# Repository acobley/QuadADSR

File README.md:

View this project on [CADLAB.io](https://cadlab.io/project/1256/master/files). 

# QuadADSR
A Quad Eurorack ADSR

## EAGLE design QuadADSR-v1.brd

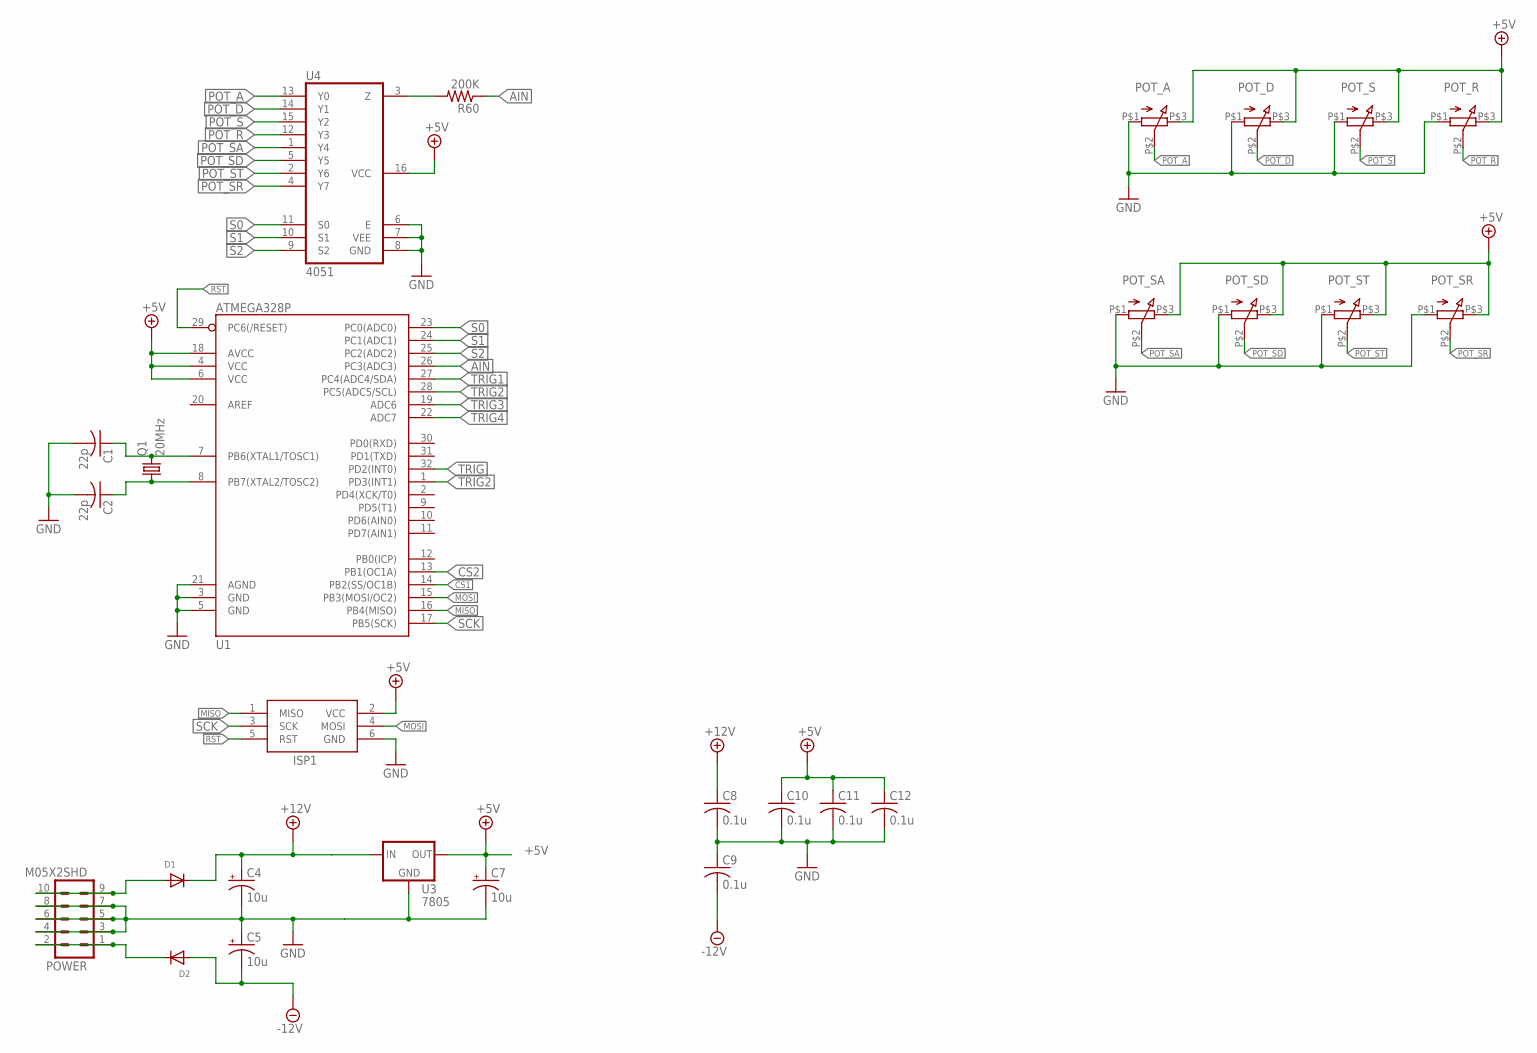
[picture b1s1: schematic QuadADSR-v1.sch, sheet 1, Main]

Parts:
C1, C2: 22p; C0805K
C4, C5, C7: 10u; 153CLV-0505
C8, C9, C10, C11, C12: 0.1u; C0805K
D1, D2: DIODESMA; SMADIODE
ISP1: AVRISP-6; AVRISP
POT_A: Q-POT
POT_D: Q-POT
POT_R: Q-POT
POT_S: Q-POT
POT_SA: Q-POT
POT_SD: Q-POT
POT_SR: Q-POT
POT_ST: Q-POT
POWER: M05X2SHD; 2X5-SHROUDED
Q1: 20MHz; HC49UP
R60: 200K; R0805
U1: ATMEGA328P; TQFP32-08
U3: 7805; V-REG
U4: 4051; N2222_ARRAY

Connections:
+5V: C7.+, C10.1, C11.1, C12.1, ISP1.2 (VCC), POT_A.P$3 (3), POT_D.P$3 (3), POT_R.P$3 (3), POT_S.P$3 (3), POT_SA.P$3 (3), POT_SD.P$3 (3), POT_SR.P$3 (3), POT_ST.P$3 (3), U1.4 (VCC), U1.6 (VCC), U1.18 (AVCC), U3.3 (OUT), U4.16 (VCC); also elsewhere on the board
+12V: C4.+, C8.1, D1.C, U3.1 (IN); also elsewhere on the board
-12V: C5.-, C9.2, D2.A; also elsewhere on the board
AIN: R60.1, U1.26 (PC3(ADC3))
CS1: U1.14 (PB2(SS/OC1B)); also elsewhere on the board
CS2: U1.13 (PB1(OC1A)); also elsewhere on the board
GND: C1.2, C2.2, C4.-, C5.+, C7.-, C8.2, C9.1, C10.2, C11.2, C12.2, ISP1.6 (GND), POT_A.P$1 (1), POT_D.P$1 (1), POT_R.P$1 (1), POT_S.P$1 (1), POT_SA.P$1 (1), POT_SD.P$1 (1), POT_SR.P$1 (1), POT_ST.P$1 (1), POWER.3, POWER.4, POWER.5, POWER.6, POWER.7, POWER.8, U1.3 (GND), U1.5 (GND), U1.21 (AGND), U3.4 (GND), U4.6 (E), U4.7 (VEE), U4.8 (GND); also elsewhere on the board
MISO: ISP1.1 (MISO), U1.16 (PB4(MISO))
MOSI: ISP1.4 (MOSI), U1.15 (PB3(MOSI/OC2)); also elsewhere on the board
unnamed: C1.1, Q1.2, U1.7 (PB6(XTAL1/TOSC1))
unnamed: C2.1, Q1.1, U1.8 (PB7(XTAL2/TOSC2))
unnamed: D1.A, POWER.9, POWER.10
unnamed: D2.C, POWER.1, POWER.2
unnamed: R60.2, U4.3 (Z)
POT_A: POT_A.P$2 (2), U4.13 (Y0)
POT_D: POT_D.P$2 (2), U4.14 (Y1)
POT_R: POT_R.P$2 (2), U4.12 (Y3)
POT_S: POT_S.P$2 (2), U4.15 (Y2)
POT_SA: POT_SA.P$2 (2), U4.1 (Y4)
POT_SD: POT_SD.P$2 (2), U4.5 (Y5)
POT_SR: POT_SR.P$2 (2), U4.4 (Y7)
POT_ST: POT_ST.P$2 (2), U4.2 (Y6)
RST: ISP1.5 (RST), U1.29 (PC6(/RESET))
S0: U1.23 (PC0(ADC0)), U4.11 (S0)
S1: U1.24 (PC1(ADC1)), U4.10 (S1)
S2: U1.25 (PC2(ADC2)), U4.9 (S2)
SCK: ISP1.3 (SCK), U1.17 (PB5(SCK)); also elsewhere on the board
TRIG: U1.32 (PD2(INT0)); also elsewhere on the board
TRIG1: U1.27 (PC4(ADC4/SDA)); also elsewhere on the board
TRIG2: U1.1 (PD3(INT1)), U1.28 (PC5(ADC5/SCL)); also elsewhere on the board
TRIG3: U1.19 (ADC6); also elsewhere on the board
TRIG4: U1.22 (ADC7); also elsewhere on the board

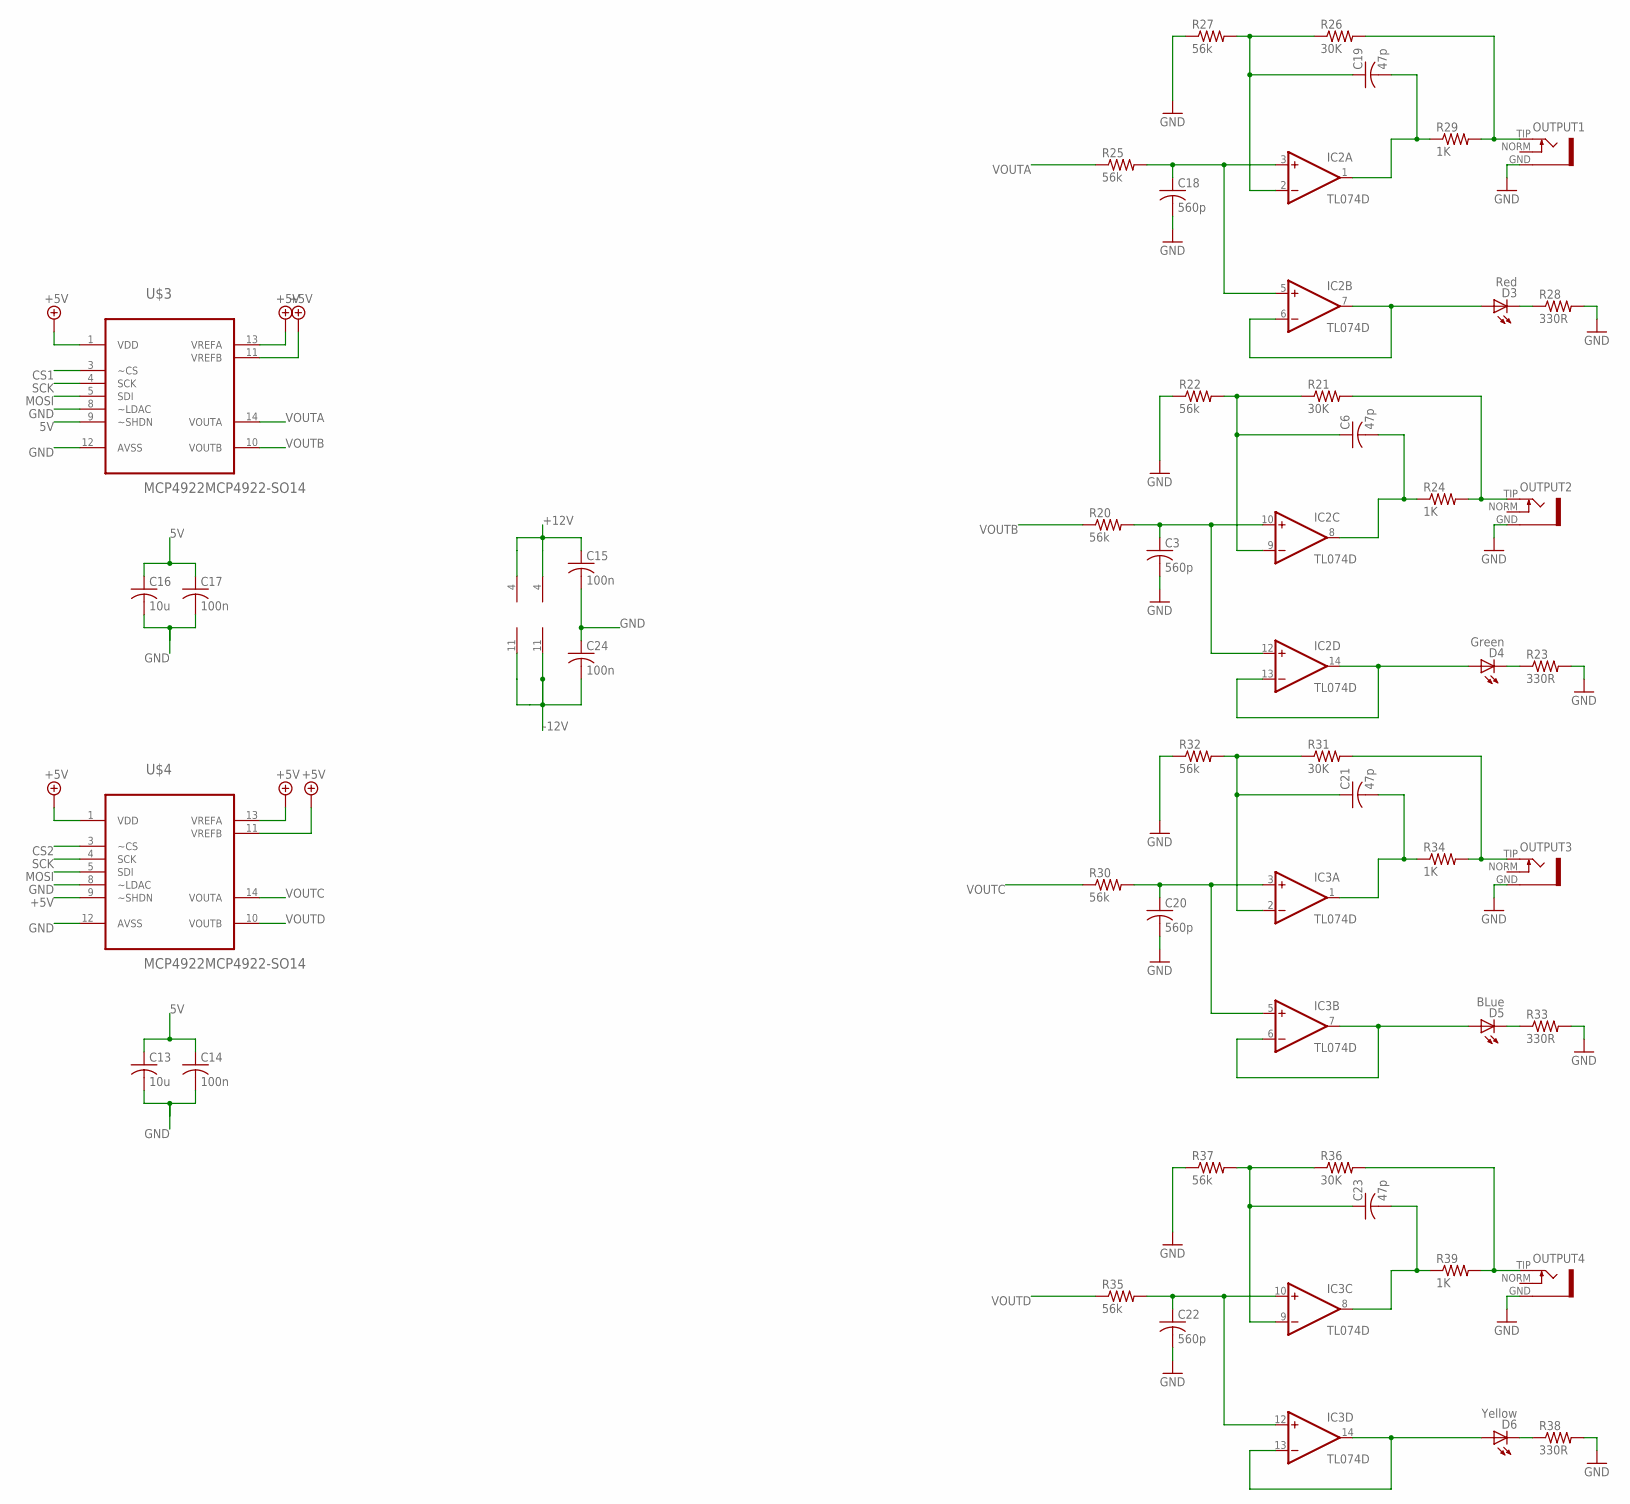
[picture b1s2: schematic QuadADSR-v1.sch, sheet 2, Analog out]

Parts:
C3, C18, C20, C22: 560p; C0805K
C6, C19, C21, C23: 47p; C0805K
C13, C16: 10u; C0805K
C14, C15, C17, C24: 100n; C0805K
D3: Red; LED5MM
D4: Green; LED5MM
D5: BLue; LED5MM
D6: Yellow; LED5MM
IC2, IC3: TL074D; SO14
OUTPUT1, OUTPUT2, OUTPUT3, OUTPUT4: S_JACK
R20, R22, R25, R27, R30, R32, R35, R37: 56k; R0805
R21, R26, R31, R36: 30K; R0805
R23, R28, R33, R38: 330R; R0805
R24, R29, R34, R39: 1K; R0805
U$3, U$4: MCP4922MCP4922-SO14; SO14

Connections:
5V: C13.1, C14.1, C16.1, C17.1, U$3.9 (~SHDN)
+5V: U$3.1 (VDD), U$3.11 (VREFB), U$3.13 (VREFA), U$4.1 (VDD), U$4.9 (~SHDN), U$4.11 (VREFB), U$4.13 (VREFA); also elsewhere on the board
+12V: C15.1, IC2.4 (V+), IC3.4 (V+); also elsewhere on the board
-12V: C24.2, IC2.11 (V-), IC3.11 (V-); also elsewhere on the board
CS1: U$3.3 (~CS); also elsewhere on the board
CS2: U$4.3 (~CS); also elsewhere on the board
GND: C3.2, C13.2, C14.2, C15.2, C16.2, C17.2, C18.2, C20.2, C22.2, C24.1, OUTPUT1.GND, OUTPUT2.GND, OUTPUT3.GND, OUTPUT4.GND, R22.1, R23.2, R27.1, R28.2, R32.1, R33.2, R37.1, R38.2, U$3.8 (~LDAC), U$3.12 (AVSS), U$4.8 (~LDAC), U$4.12 (AVSS); also elsewhere on the board
MOSI: U$3.5 (SDI), U$4.5 (SDI); also elsewhere on the board
unnamed: C3.1, IC2.10 (+IN), IC2.12 (+IN), R20.2
unnamed: C6.1, IC2.9 (-IN), R21.1, R22.2
unnamed: OUTPUT2.TIP, R21.2, R24.2
unnamed: D4.A, IC2.13 (-IN), IC2.14 (OUT)
unnamed: D4.K (C), R23.1
unnamed: C6.2, IC2.8 (OUT), R24.1
unnamed: C18.1, IC2.3 (+IN), IC2.5 (+IN), R25.2
unnamed: C19.1, IC2.2 (-IN), R26.1, R27.2
unnamed: OUTPUT1.TIP, R26.2, R29.2
unnamed: D3.A, IC2.6 (-IN), IC2.7 (OUT)
unnamed: D3.K (C), R28.1
unnamed: C19.2, IC2.1 (OUT), R29.1
unnamed: C20.1, IC3.3 (+IN), IC3.5 (+IN), R30.2
unnamed: C21.1, IC3.2 (-IN), R31.1, R32.2
unnamed: OUTPUT3.TIP, R31.2, R34.2
unnamed: D5.A, IC3.6 (-IN), IC3.7 (OUT)
unnamed: D5.K (C), R33.1
unnamed: C21.2, IC3.1 (OUT), R34.1
unnamed: C22.1, IC3.10 (+IN), IC3.12 (+IN), R35.2
unnamed: C23.1, IC3.9 (-IN), R36.1, R37.2
unnamed: OUTPUT4.TIP, R36.2, R39.2
unnamed: D6.A, IC3.13 (-IN), IC3.14 (OUT)
unnamed: D6.K (C), R38.1
unnamed: C23.2, IC3.8 (OUT), R39.1
SCK: U$3.4 (SCK), U$4.4 (SCK); also elsewhere on the board
VOUTA: R25.1, U$3.14 (VOUTA)
VOUTB: R20.1, U$3.10 (VOUTB)
VOUTC: R30.1, U$4.14 (VOUTA)
VOUTD: R35.1, U$4.10 (VOUTB)

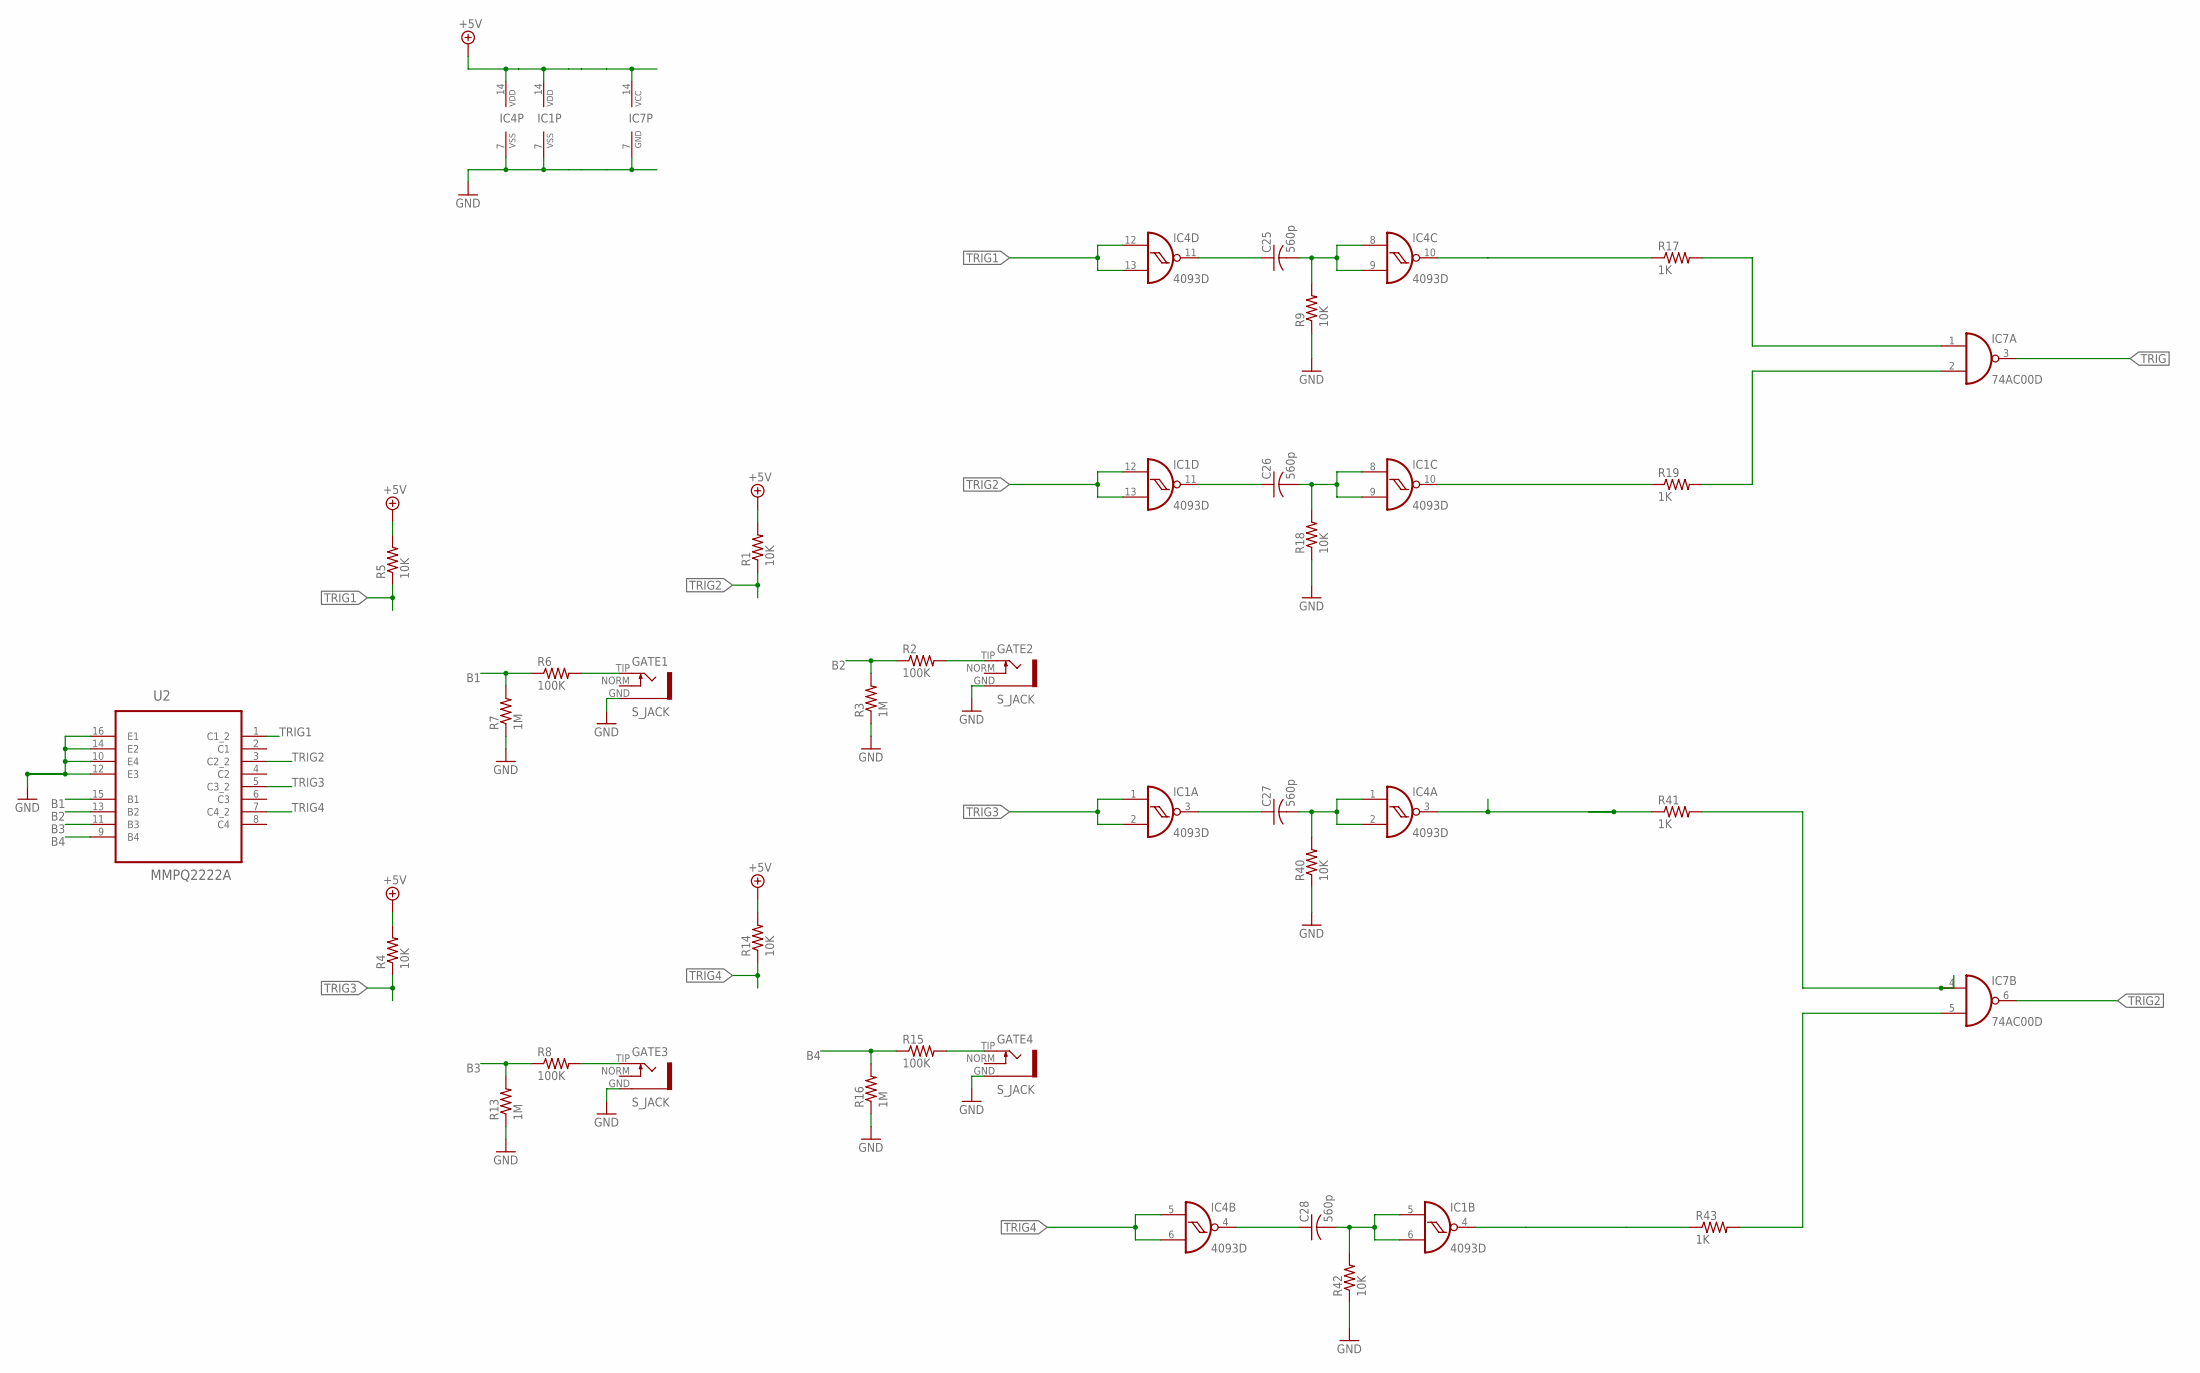
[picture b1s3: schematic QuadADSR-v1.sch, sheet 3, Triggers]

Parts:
C25, C26, C27, C28: 560p; C0805K
GATE1, GATE2, GATE3, GATE4: S_JACK
IC1, IC4: 4093D; SO14
IC7: 74AC00D; SO14
R1, R4, R5, R9, R14, R18, R40, R42: 10K; R0805
R2, R6, R8, R15: 100K; R0805
R3, R7, R13, R16: 1M; R0805
R17, R19, R41, R43: 1K; R0805
U2: MMPQ2222A; SOIC127P600X175-16N

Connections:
+5V: IC1.14 (VDD), IC4.14 (VDD), IC7.14 (VCC), R1.2, R4.2, R5.2, R14.2; also elsewhere on the board
B1: R6.1, R7.2, U2.15 (B1)
B2: R2.1, R3.2, U2.13 (B2)
B3: R8.1, R13.2, U2.11 (B3)
B4: R15.1, R16.2, U2.9 (B4)
GND: GATE1.GND, GATE2.GND, GATE3.GND, GATE4.GND, IC1.7 (VSS), IC4.7 (VSS), IC7.7 (GND), R3.1, R7.1, R9.1, R13.1, R16.1, R18.1, R40.1, R42.1, U2.10 (E4), U2.12 (E3), U2.14 (E2), U2.16 (E1); also elsewhere on the board
unnamed: GATE2.TIP, R2.2
unnamed: GATE3.TIP, R8.2
unnamed: GATE4.TIP, R15.2
unnamed: C26.2, IC1.8 (I0), IC1.9 (I1), R18.2
unnamed: IC1.10 (O), R19.1
unnamed: GATE1.TIP, R6.2
unnamed: C25.2, IC4.8 (I0), IC4.9 (I1), R9.2
unnamed: IC4.10 (O), R17.1
unnamed: C25.1, IC4.11 (O)
unnamed: C26.1, IC1.11 (O)
unnamed: C27.2, IC4.1 (I0), IC4.2 (I1), R40.2
unnamed: IC4.3 (O), R41.1
unnamed: C27.1, IC1.3 (O)
unnamed: C28.2, IC1.5 (I0), IC1.6 (I1), R42.2
unnamed: IC1.4 (O), R43.1
unnamed: C28.1, IC4.4 (O)
PULSE1: IC7.1 (I0), R17.2
PULSE2: IC7.2 (I1), R19.2
PULSE3: IC7.4 (I0), R41.2
PULSE4: IC7.5 (I1), R43.2
TRIG: IC7.3 (O); also elsewhere on the board
TRIG1: IC4.12 (I0), IC4.13 (I1), R5.1, U2.1 (C1_2); also elsewhere on the board
TRIG2: IC1.12 (I0), IC1.13 (I1), IC7.6 (O), R1.1, U2.3 (C2_2); also elsewhere on the board
TRIG3: IC1.1 (I0), IC1.2 (I1), R4.1, U2.5 (C3_2); also elsewhere on the board
TRIG4: IC4.5 (I0), IC4.6 (I1), R14.1, U2.7 (C4_2); also elsewhere on the board

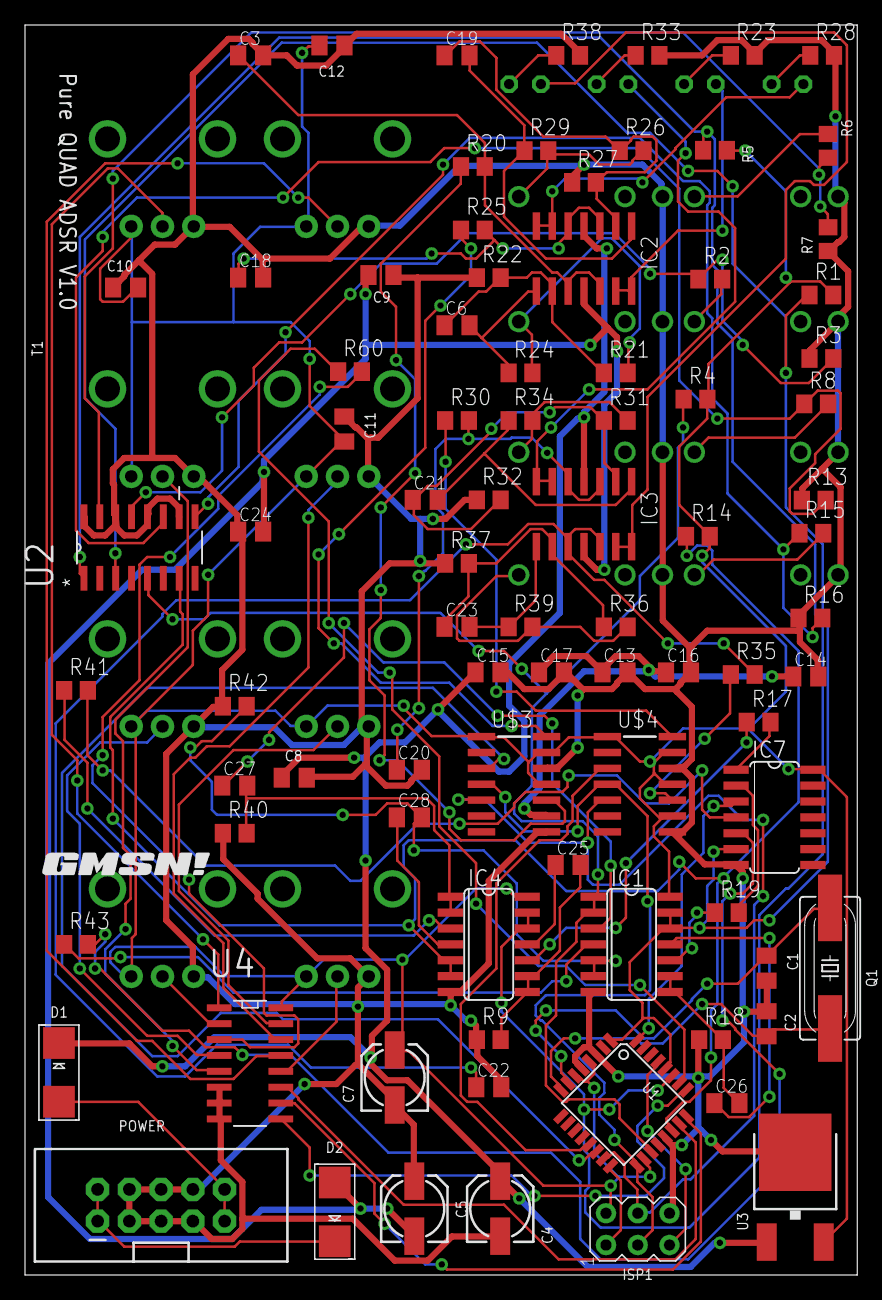
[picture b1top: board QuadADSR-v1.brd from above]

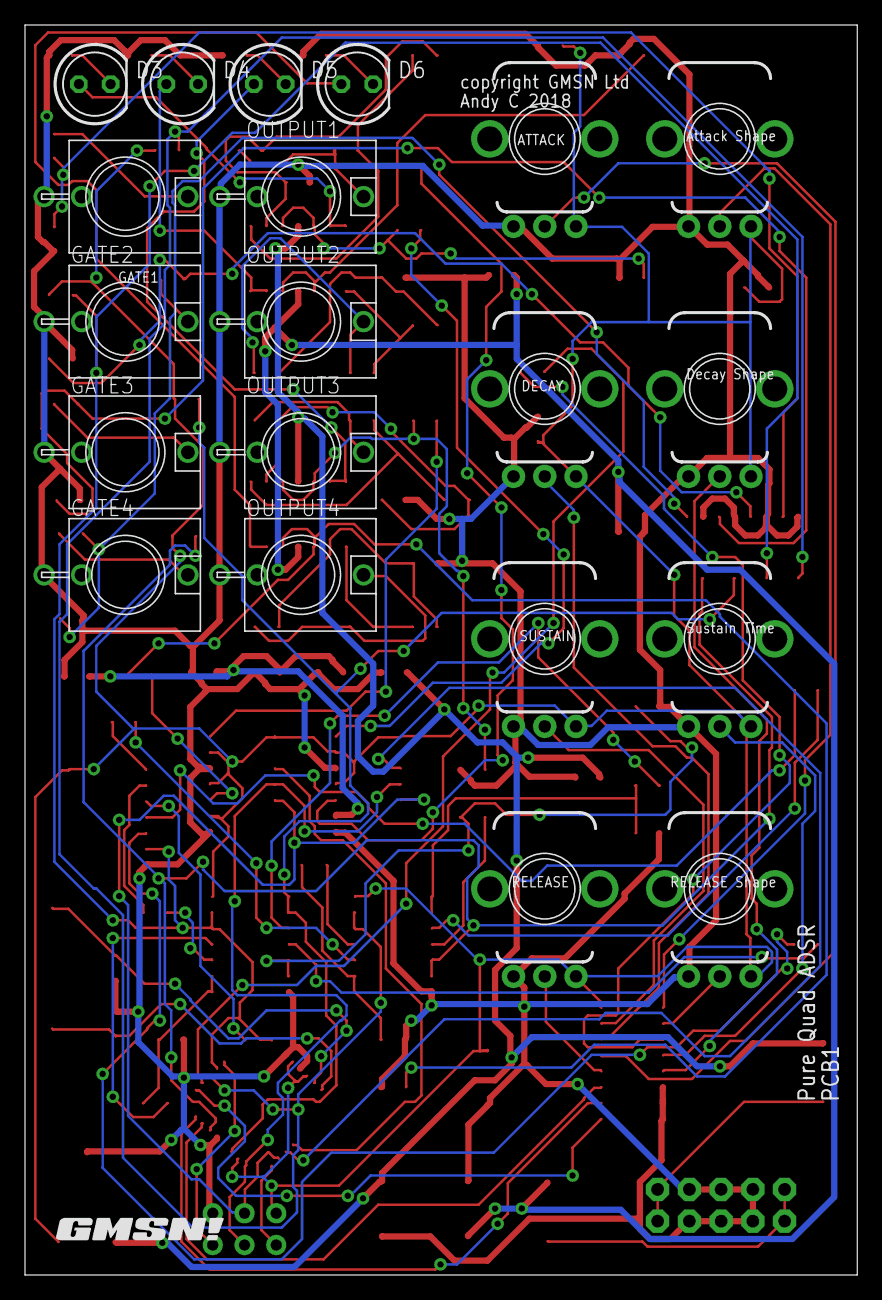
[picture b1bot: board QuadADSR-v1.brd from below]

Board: 2 copper layers, 66.6 x 100.0 mm, 107 parts (21 on the bottom side), 85 nets.

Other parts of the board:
U$1, U$2: GMSN!_LOGO

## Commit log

2018-08-10 Initial Push
2018-08-10 Initial Board Layout
2018-08-13 Layed out board with shape pots
2018-08-13 Moved a few thigs round
2018-08-13 reroute
2018-08-13 updated Graphics
2018-08-16 updated TEXT Graphics
2018-08-18 added V1 Board
2018-08-19 Added sheet names
2018-08-23 using GMSN! output table
2018-09-25 removed Switch and checked Schmitt
2018-09-25 Quad Transistor

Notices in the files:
QuadADSR-v1.brd:
copyright GMSN Ltd
parts and their libraries:
SparkFun-Connectors: Licensing: CC v3.0 Share-Alike You are welcome to use this library for commercial purposes.
